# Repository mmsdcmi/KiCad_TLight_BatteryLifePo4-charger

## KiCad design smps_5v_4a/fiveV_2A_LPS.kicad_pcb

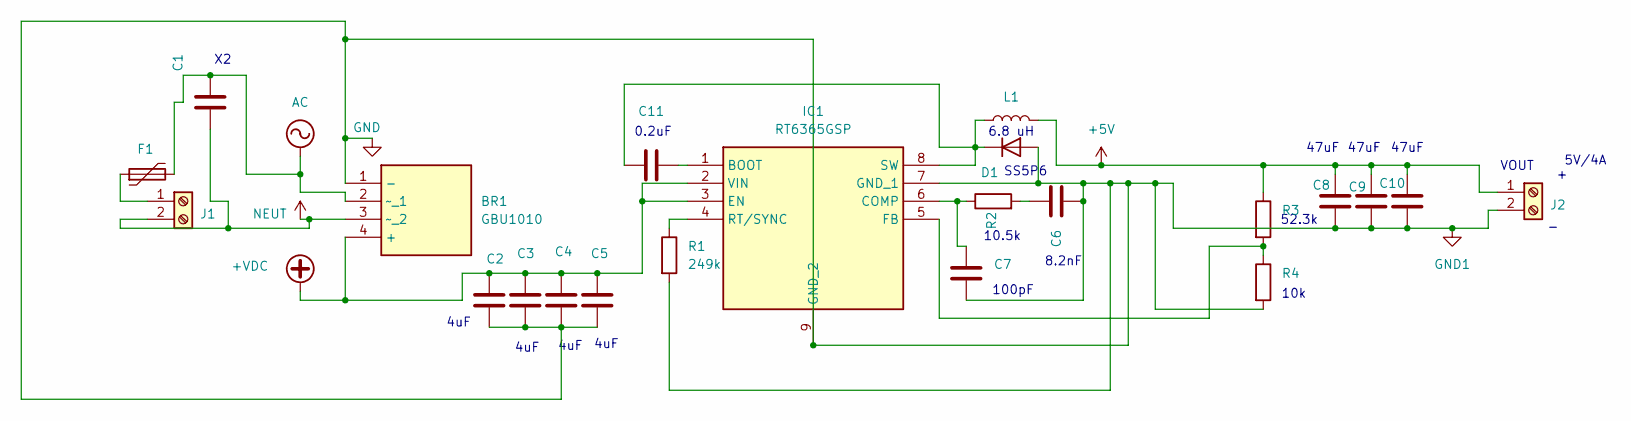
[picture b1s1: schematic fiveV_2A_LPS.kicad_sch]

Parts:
BR1: GBU1010; TO508P356X2205X2135-4P; Manufacturer_Part_Number GBU1010; Mouser Part Number 621-GBU1010
C1: C; C_2220_5750Metric
C2, C3, C4, C5: C; C_1206_3216Metric_Pad1.33x1.80mm_HandSolder
C6: C; C_0805_2012Metric_Pad1.18x1.45mm_HandSolder
C7: C; C_0402_1005Metric_Pad0.74x0.62mm_HandSolder
C8, C9, C10: C; C_1812_4532Metric_Pad1.57x3.40mm_HandSolder
C11: C; C_0603_1608Metric_Pad1.08x0.95mm_HandSolder
D1: D; TO-277A
F1: Polyfuse; Fuse_Bourns_MF-RG600
IC1: RT6365GSP; SOIC127P600X175-9N; Manufacturer_Part_Number RT6365GSP; Mouser Part Number 835-RT6365GSP
J1, J2: Screw_Terminal_01x02; TerminalBlock_MetzConnect_Type205_RT04502UBLC_1x02_P5.00mm_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
L1: L; L_Taiyo-Yuden_NR-60xx
R1: 249k; R_1206_3216Metric_Pad1.30x1.75mm_HandSolder
R2, R3, R4: R; R_0603_1608Metric_Pad0.98x0.95mm_HandSolder

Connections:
+5V: C8.1, C9.1, C10.1, J2.1, L1.2, R3.1
+VDC: BR1.4 (+), C2.1, C3.1, C4.1, C5.1, IC1.2 (VIN), IC1.3 (EN)
AC: BR1.2 (~_1), C1.2, F1.2
GND: BR1.1 (-), C2.2, C3.2, C4.2, C5.2, C6.2, C7.2, C8.2, C9.2, C10.2, D1.2 (A), IC1.7 (GND_1), IC1.9 (GND_2), J2.2, R1.2, R4.2
NEUT: BR1.3 (~_2), C1.1, J1.2
unnamed: C6.1, R2.2
unnamed: C11.2, D1.1 (K), IC1.8 (SW), L1.1
unnamed: C11.1, IC1.1 (BOOT)
unnamed: C7.1, IC1.6 (COMP), R2.1
unnamed: IC1.5 (FB), R3.2, R4.1
unnamed: IC1.4 (RT/SYNC), R1.1
unnamed: F1.1, J1.1

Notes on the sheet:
47uF
VOUT
8.2nF
10.5k
0.2uF
6.8 uH
4uF
SS5P6
5V/4A
10k
100pF
52.3k

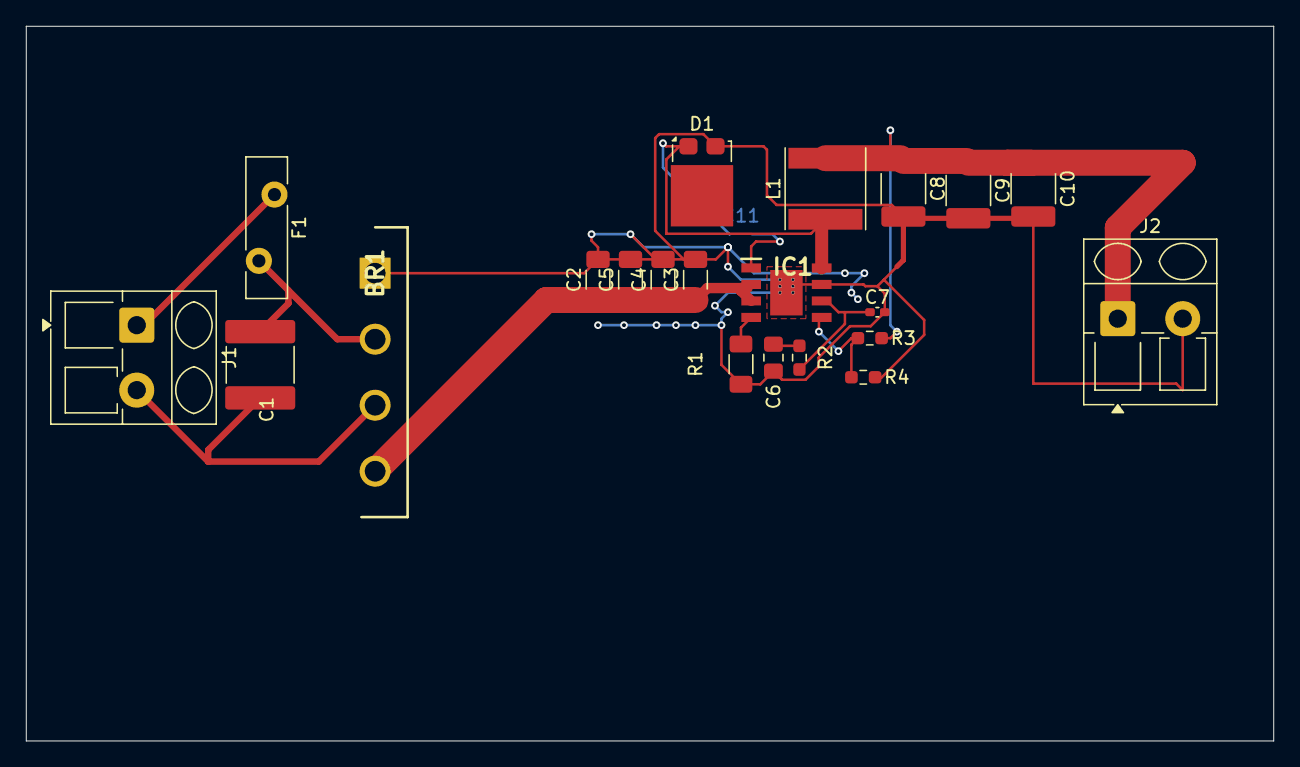
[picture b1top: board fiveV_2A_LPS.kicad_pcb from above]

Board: 2 copper layers, 96.0 x 55.0 mm, 22 parts (1 on the bottom side), 12 nets.

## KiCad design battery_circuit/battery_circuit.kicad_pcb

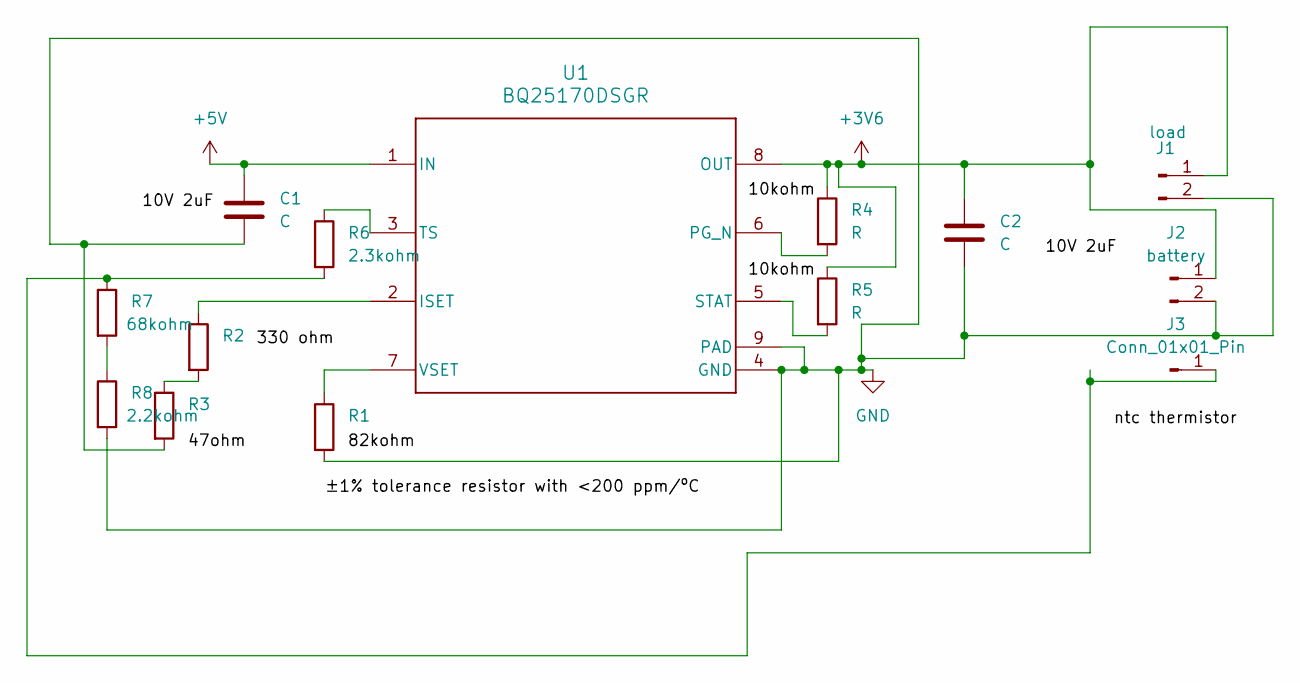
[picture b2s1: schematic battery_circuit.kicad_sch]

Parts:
C1, C2: C; C_0603_1608Metric
J1: load; PinHeader_1x02_P1.27mm_Vertical
J2: battery; PinHeader_1x02_P1.27mm_Vertical
J3: Conn_01x01_Pin; PinHeader_1x01_P1.27mm_Vertical
R1: R; R_1206_3216Metric
R2: R; R_1206_3216Metric_Pad1.30x1.75mm_HandSolder
R3: R; R_2010_5025Metric_Pad1.40x2.65mm_HandSolder
R4, R5: R; R_Axial_DIN0204_L3.6mm_D1.6mm_P2.54mm_Vertical
R6: 2.3kohm; R_0402_1005Metric_Pad0.72x0.64mm_HandSolder
R7: 68kohm; R_Axial_DIN0309_L9.0mm_D3.2mm_P12.70mm_Horizontal
R8: 2.2kohm; R_Axial_DIN0309_L9.0mm_D3.2mm_P12.70mm_Horizontal
U1: BQ25170DSGR; DSG0008A

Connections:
+3V6: C2.1, J1.1, J2.1, R4.1, R5.1, U1.8 (OUT)
+5V: C1.1, U1.1 (IN)
GND: C1.2, C2.2, J1.2, J2.2, R1.2, R3.2, R8.2, U1.4 (GND), U1.9 (PAD), U1.10, U1.11
unnamed: J3.1, R6.2, R7.1
unnamed: R2.2, R3.1
unnamed: R7.2, R8.1
unnamed: R2.1, U1.2 (ISET)
unnamed: R4.2, U1.6 (PG_N)
unnamed: R5.2, U1.5 (STAT)
unnamed: R6.1, U1.3 (TS)
unnamed: R1.1, U1.7 (VSET)

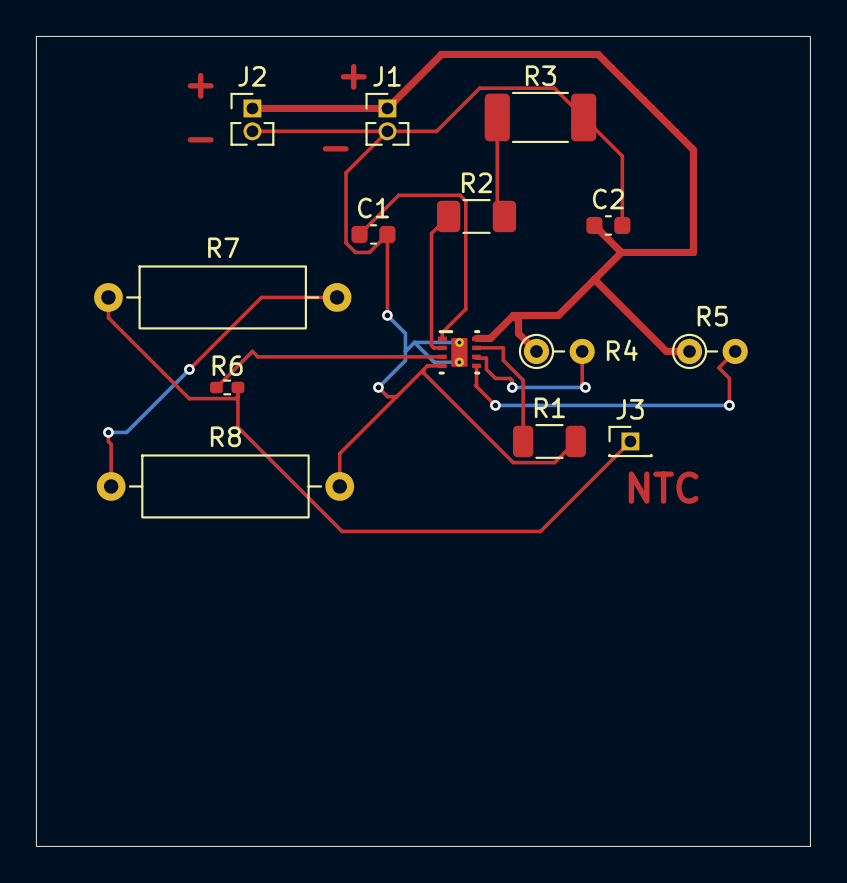
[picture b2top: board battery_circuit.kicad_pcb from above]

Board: 2 copper layers, 43.0 x 45.0 mm, 14 parts (0 on the bottom side), 11 nets.

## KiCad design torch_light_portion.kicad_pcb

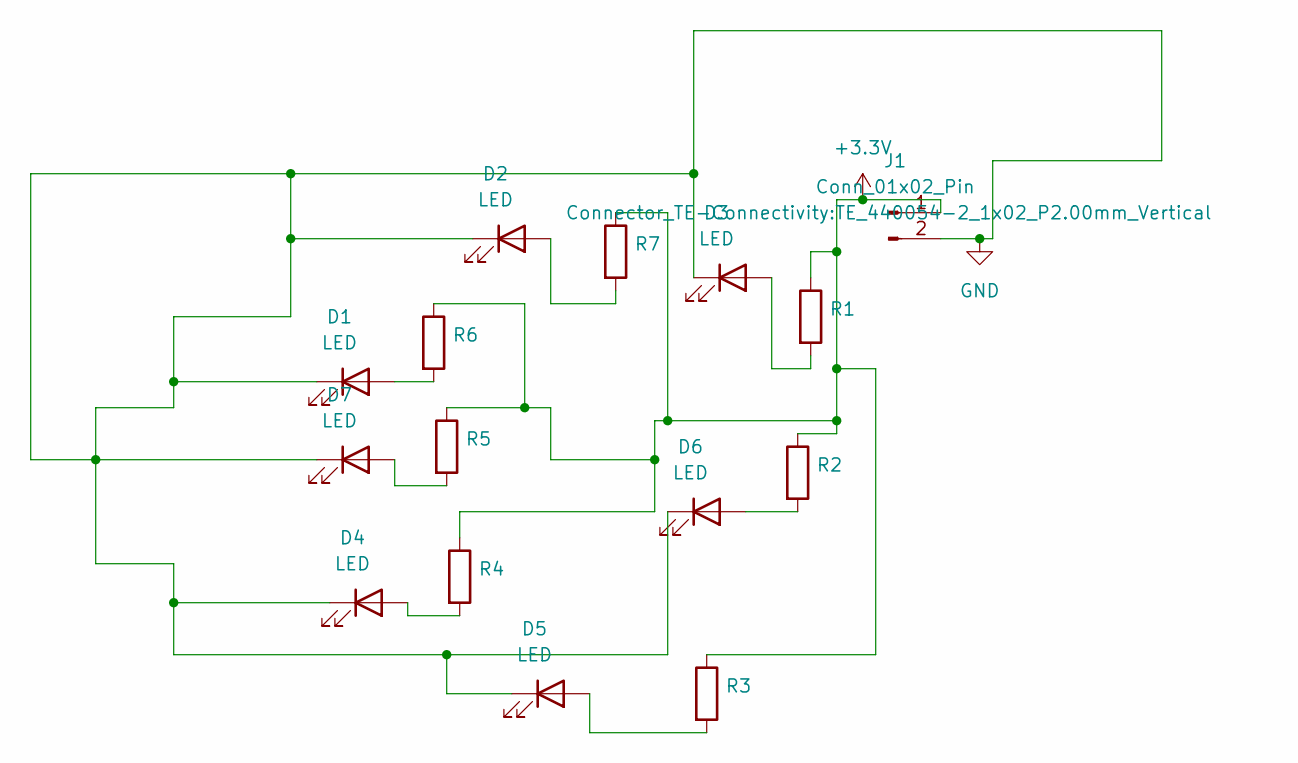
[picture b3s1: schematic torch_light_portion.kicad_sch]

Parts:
D1, D2, D3, D4, D5, D6, D7: LED; LED_Everlight-SMD3528_3.5x2.8mm_67-21ST
J1: Conn_01x02_Pin; TE_440054-2_1x02_P2.00mm_Vertical
R1, R2, R3, R4, R5, R6, R7: R; R_0603_1608Metric

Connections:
+3.3V: J1.1, R1.1, R2.1, R3.1, R4.1, R5.1, R6.1, R7.1
GND: D1.1 (K), D2.1 (K), D3.1 (K), D4.1 (K), D5.1 (K), D6.1 (K), D7.1 (K), J1.2
unnamed: D1.2 (A), R6.2
unnamed: D2.2 (A), R7.2
unnamed: D3.2 (A), R1.2
unnamed: D4.2 (A), R4.2
unnamed: D5.2 (A), R3.2
unnamed: D6.2 (A), R2.2
unnamed: D7.2 (A), R5.2

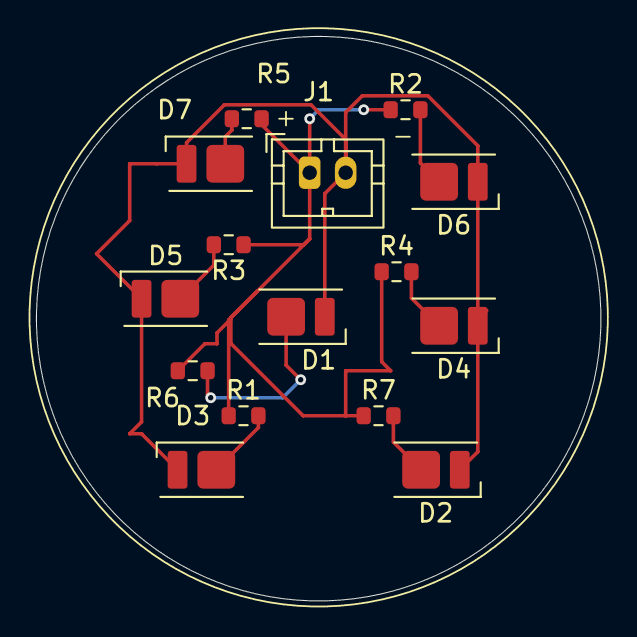
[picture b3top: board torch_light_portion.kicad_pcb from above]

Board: 2 copper layers, 31.4 x 31.4 mm, 15 parts (0 on the bottom side), 9 nets.
